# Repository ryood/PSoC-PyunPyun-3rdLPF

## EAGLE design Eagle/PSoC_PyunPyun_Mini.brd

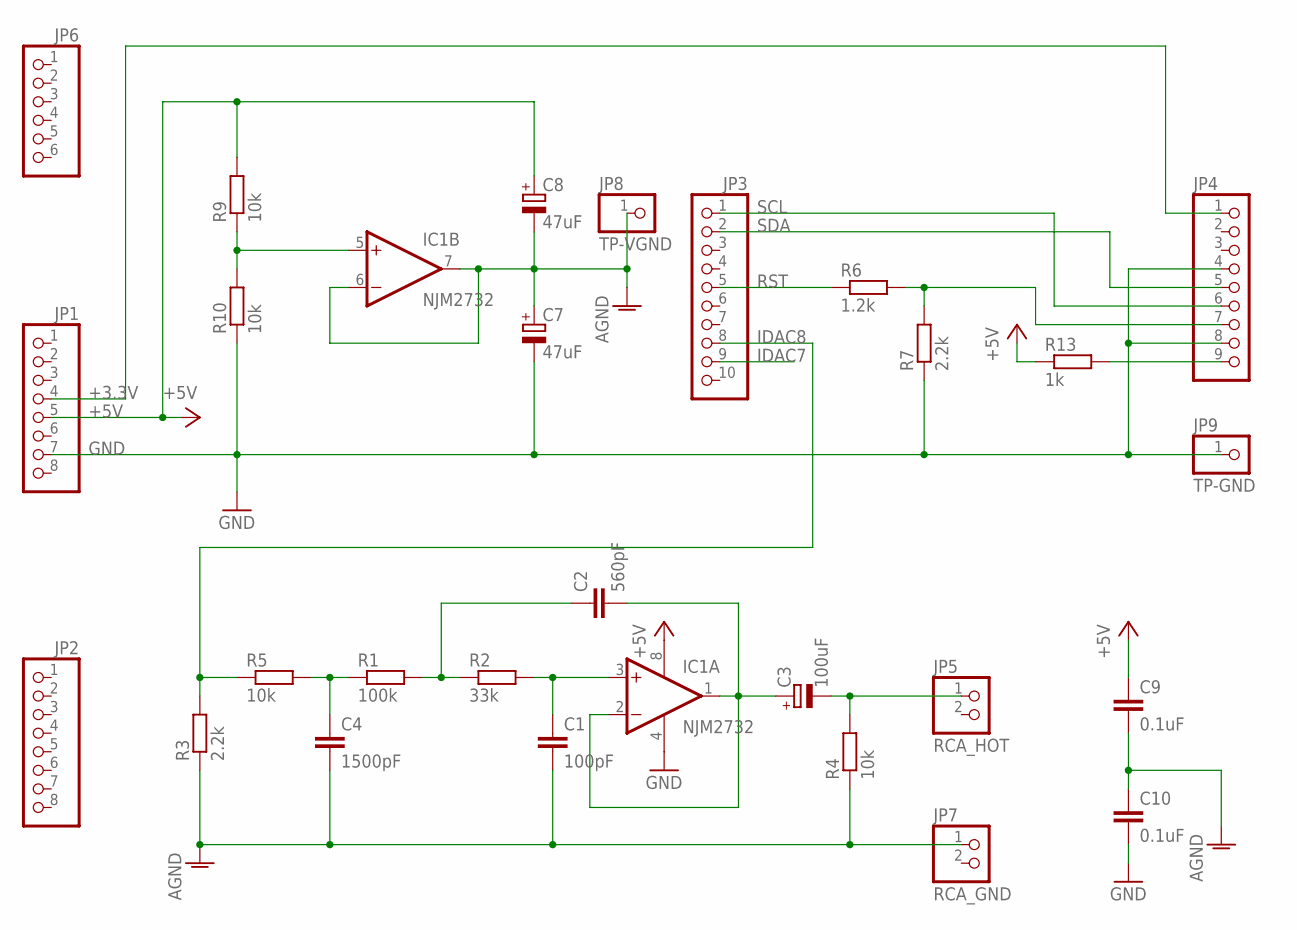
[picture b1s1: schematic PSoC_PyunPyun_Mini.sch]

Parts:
C1: 100pF; C050-024X044
C2: 560pF; C050-024X044
C3: 100uF; E2,5-7
C4: 1500pF; C050-024X044
C7, C8: 47uF; E2,5-5
C9, C10: 0.1uF; C050-024X044
IC1: NJM2732; DIL08
JP1, JP2: PINHD-1X8; 1X08
JP3: PINHD-1X10; 1X10
JP4: PINHD-1X9; 1X09
JP5: RCA_HOT; 1X02
JP6: PINHD-1X6; 1X06
JP7: RCA_GND; 1X02
JP8: TP-VGND; 1X01
JP9: TP-GND; 1X01
R1: 100k; 0207/7
R2: 33k; 0207/7
R3, R7: 2.2k; 0207/7
R4, R5, R9, R10: 10k; 0207/7
R6: 1.2k; 0207/7
R13: 1k; 0207/7

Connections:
+3.3V: JP1.4, JP4.1
+5V: C8.+, C9.1, IC1.8 (V+), JP1.5, R9.2, R13.1
AGND: C1.2, C4.2, C7.+, C8.-, C9.2, C10.1, IC1.6 (-IN), IC1.7 (OUT), JP7.1, JP8.1, R3.1, R4.1
GND: C7.-, C10.2, IC1.4 (V-), JP1.7, JP4.4, JP4.8, JP9.1, R7.1, R10.1
IDAC7: JP3.9
IDAC8: JP3.8, R3.2, R5.1
unnamed: C2.1, R1.2, R2.1
unnamed: C4.1, R1.1, R5.2
unnamed: C1.1, IC1.3 (+IN), R2.2
unnamed: C2.2, C3.+, IC1.1 (OUT), IC1.2 (-IN)
unnamed: JP4.9, R13.2
unnamed: JP3.5, R6.1
unnamed: C3.-, JP5.1, R4.2
unnamed: IC1.5 (+IN), R9.1, R10.2
RST: JP4.7, R6.2, R7.2
SCL: JP3.1, JP4.6
SDA: JP3.2, JP4.5

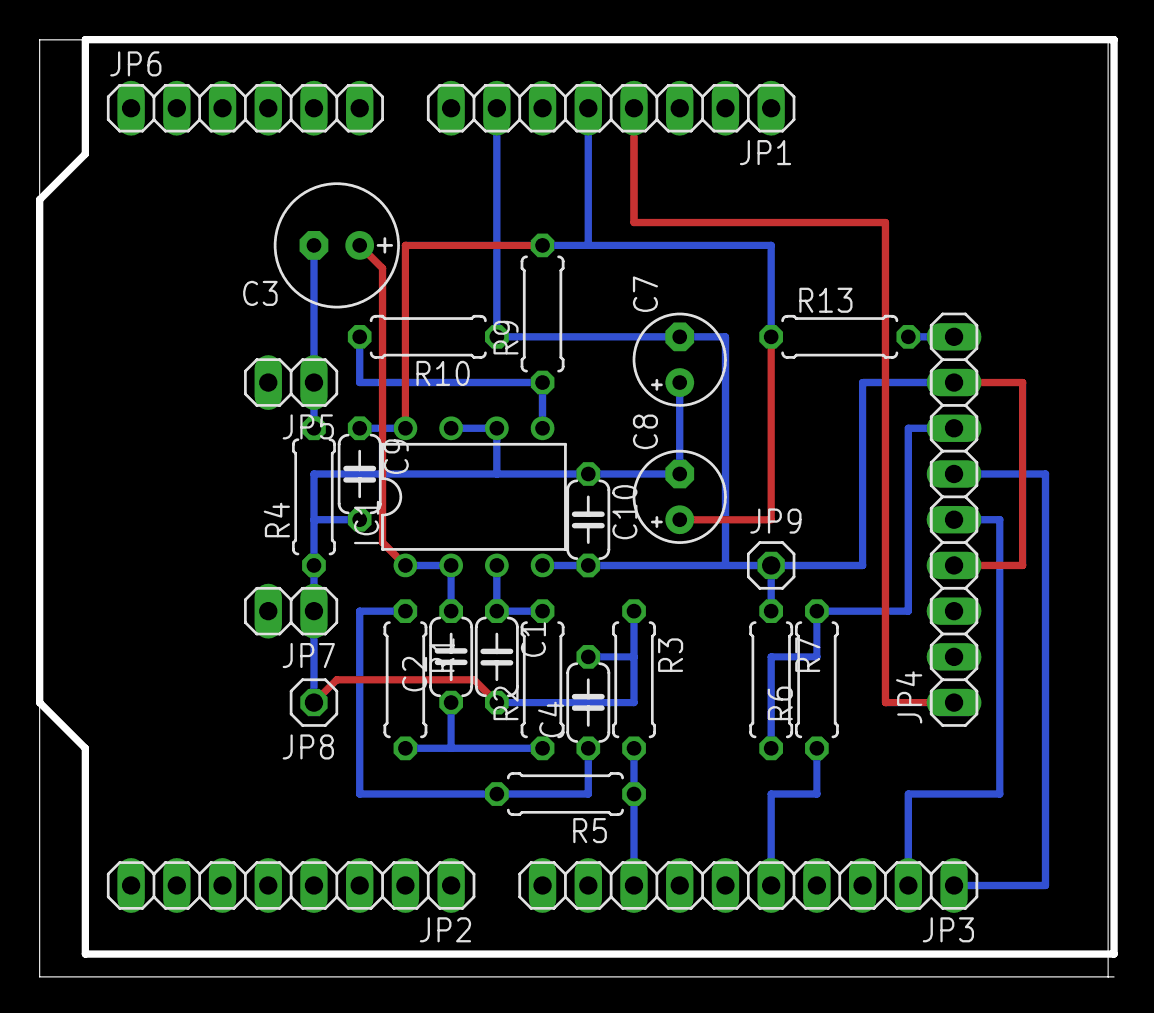
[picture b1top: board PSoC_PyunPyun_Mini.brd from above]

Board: 2 copper layers, 59.7 x 51.9 mm, 28 parts (0 on the bottom side), 16 nets.

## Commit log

2015-04-10 change Bord Design
2015-04-23 回路図・基板図 RST信号に抵抗分圧を追加
2015-04-23 基板設計図 RST信号の分圧抵抗の位置を変更
2015-04-28 シールドの製作完了
2015-06-13 PyunPyun3_Test.xlsx: テスト表追加
2015-06-13 main.c: 最大周波数を2000kHzに変更
2015-06-13 Backup: PSoC Creatorのバージョンアップに伴うBackupを追加
2015-06-23 main.c wavetable.h: 909Kickの波形を追加
2015-07-29 branch for pyun2contoller2
2015-08-01 Add: Backup\PSoC_PyunPyun_3rdLPF-000._3.2_SP2.zip
2015-08-01 Add 808 Conga Wave
2015-08-01 Update to waveTableStep
2015-08-06 Change: Backup\PSoc_PyunPyun_3rdLPF-000._3.1_SP2.zip
